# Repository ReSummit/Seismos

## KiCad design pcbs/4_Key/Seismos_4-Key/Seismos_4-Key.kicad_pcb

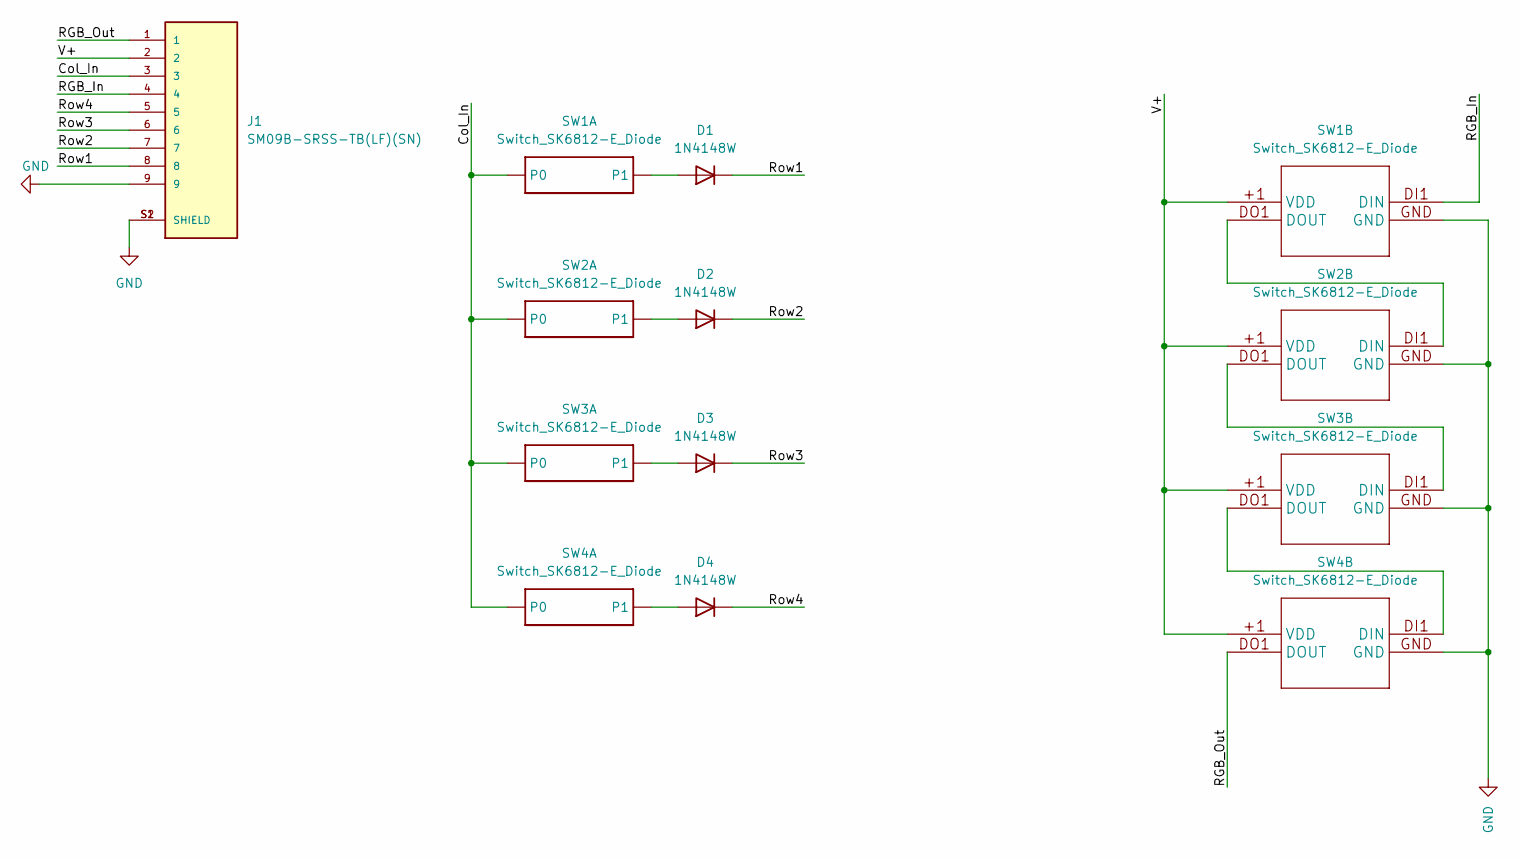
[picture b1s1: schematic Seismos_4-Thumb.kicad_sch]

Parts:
D1, D2, D3, D4: 1N4148W; D_SOD-123
J1: SM09B-SRSS-TB(LF)(SN); JST_SM09B-SRSS-TB(LF)(SN); PARTREV 1.0
SW1, SW2, SW3, SW4: Switch_SK6812-E_Diode

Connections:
/Col_In: J1.3, SW1.CHOC2 (P0), SW1.MX2 (P0), SW2.CHOC2 (P0), SW2.MX2 (P0), SW3.CHOC2 (P0), SW3.MX2 (P0), SW4.CHOC2 (P0), SW4.MX2 (P0)
/RGB_In: J1.4, SW1.DI1 (DIN)
/RGB_Out: J1.1, SW4.DO1 (DOUT)
/Row1: D1.1 (K), J1.8
/Row2: D2.1 (K), J1.7
/Row3: D3.1 (K), J1.6
/Row4: D4.1 (K), J1.5
/V+: J1.2, SW1.+1 (VDD), SW2.+1 (VDD), SW3.+1 (VDD), SW4.+1 (VDD)
GND: J1.9, J1.S1 (SHIELD), J1.S2 (SHIELD), SW1.GND, SW2.GND, SW3.GND, SW4.GND
unnamed: D1.2 (A), SW1.CHOC1 (P1), SW1.MX1 (P1)
unnamed: D2.2 (A), SW2.CHOC1 (P1), SW2.MX1 (P1)
unnamed: D3.2 (A), SW3.CHOC1 (P1), SW3.MX1 (P1)
unnamed: D4.2 (A), SW4.CHOC1 (P1), SW4.MX1 (P1)
unnamed: SW1.DO1 (DOUT), SW2.DI1 (DIN)
unnamed: SW2.DO1 (DOUT), SW3.DI1 (DIN)
unnamed: SW3.DO1 (DOUT), SW4.DI1 (DIN)

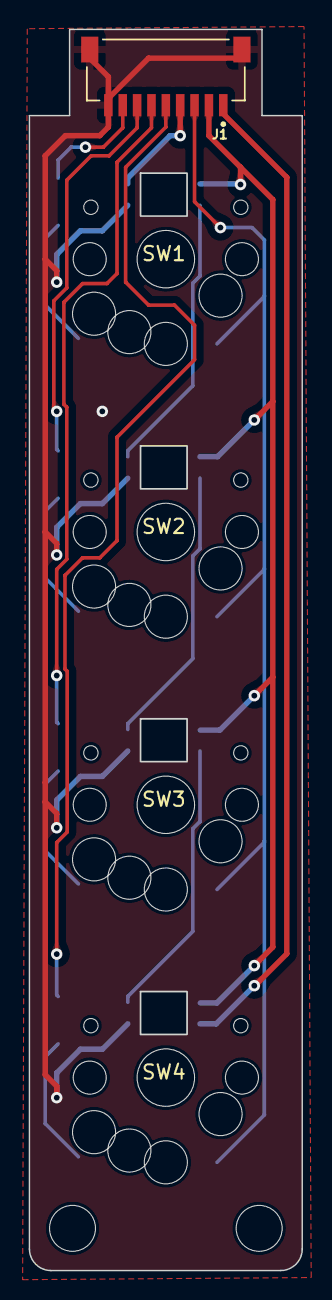
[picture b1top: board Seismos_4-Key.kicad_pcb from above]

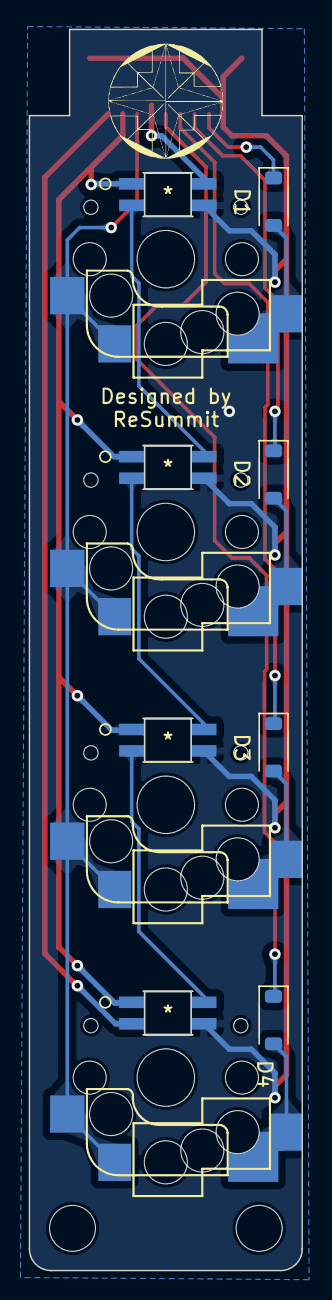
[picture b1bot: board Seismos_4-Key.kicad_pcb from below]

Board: 2 copper layers, 19.0 x 86.4 mm, 9 parts (4 on the bottom side), 16 nets.

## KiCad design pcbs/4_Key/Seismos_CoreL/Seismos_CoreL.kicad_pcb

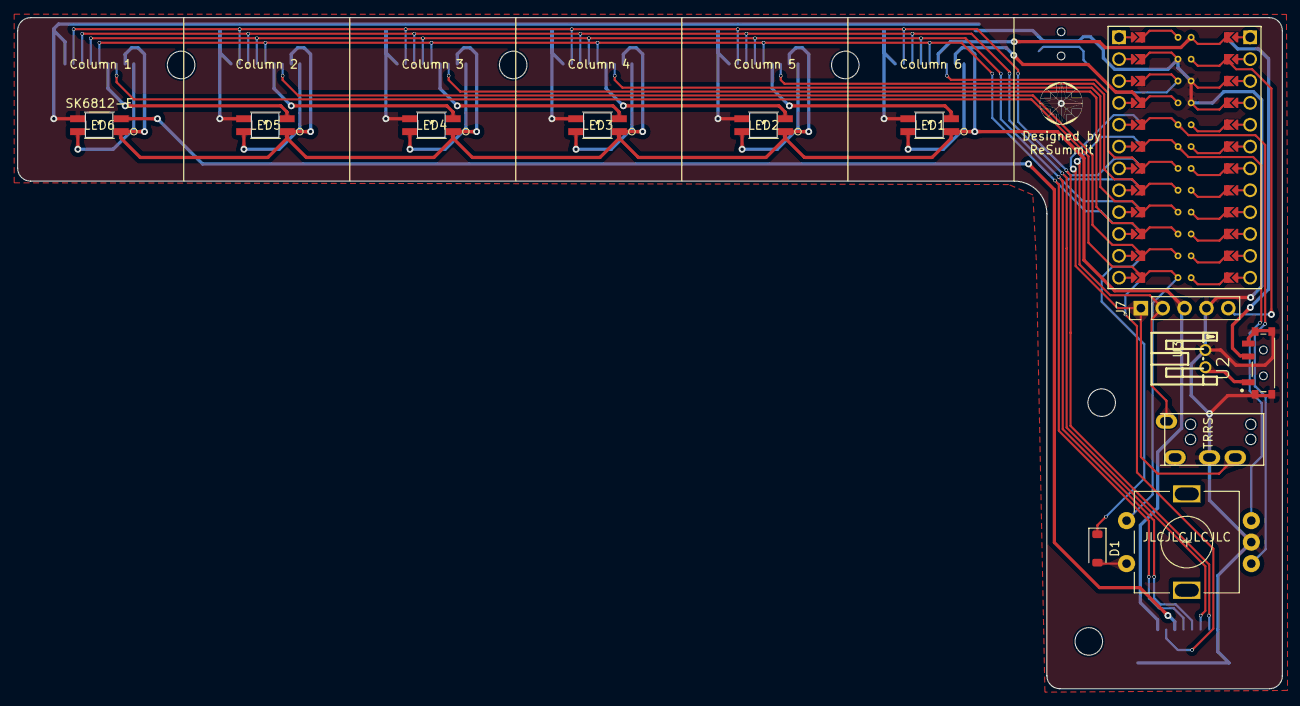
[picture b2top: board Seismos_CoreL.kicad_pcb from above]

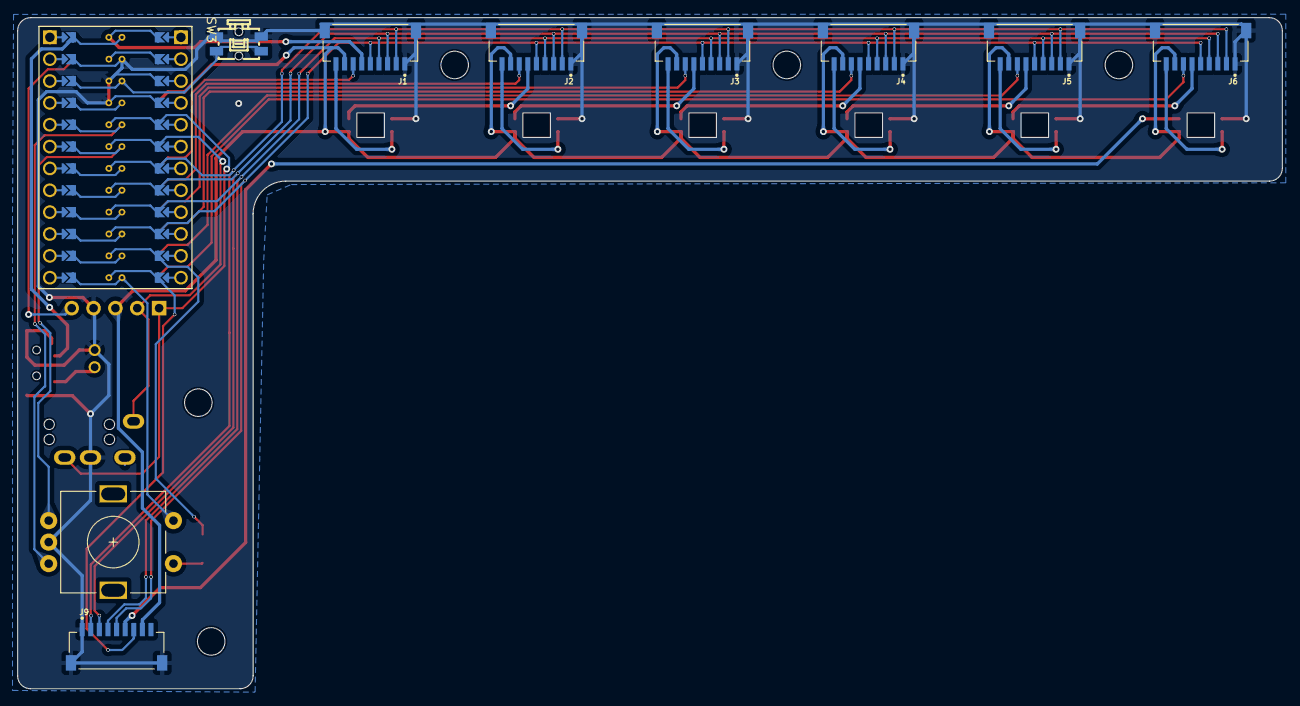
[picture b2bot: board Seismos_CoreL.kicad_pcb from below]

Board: 2 copper layers, 147.0 x 78.0 mm, 23 parts (14 on the bottom side), 36 nets.

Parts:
2, 4: Hole_M3_3.2mm
D1: 1N4148W; D_SOD-123
J1, J2, J3, J4, J5, J6, J9: SM09B-SRSS-TB(LF)(SN); JST_SM09B-SRSS-TB(LF)(SN)
J7: Conn_01x05_Pin; PinHeader_1x05_P2.54mm_Vertical
J8: MJ-4PP-9-Lily58; MJ-4PP-9
LED1, LED2, LED3, LED4, LED5, LED6: SK6812-E
SW1: RotaryEncoder_Switch; RotaryEncoder_Alps_EC11E-Switch_Vertical_H20mm-keebio_modif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
SW3: EVQPUC02K; SW-SMD_EVQPUD02K
U1: ProMicro_2-Lily58-cache-Lily58_Pro-rescue; ProMicro
U2: MSK-12C02_SMD_SPDT_SWITCH; SW_PCM12SMTR
U3: S2B-PH-K-S-GW; CONN-TH_S2B-PH-K-S-GW

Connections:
/Col_In1: J1.7, U1.18 (A1(PF6))
/Col_In2: J2.7, U1.17 (A0(PF7))
/Col_In3: J3.7, U1.16 (D15(PB1))
/Col_In4: J4.7, U1.15 (D14(PB3))
/Col_In5: J5.7, U1.14 (D16(PB2))
/Col_In6: J6.7, SW1.S1, U1.13 (D10(PB6))
/Col_InT: J9.7, U1.12 (D9(PB5))
/RGB_In1: J1.6, U1.1 (TX(PD3))
/RGB_In2: J2.6, LED1.2 (DOUT)
/RGB_In3: J3.6, LED2.2 (DOUT)
/RGB_In4: J4.6, LED3.2 (DOUT)
/RGB_In5: J5.6, LED4.2 (DOUT)
/RGB_In6: J6.6, LED5.2 (DOUT)
/RGB_In7: J9.6, LED6.2 (DOUT)
/RGB_Out1: J1.9, LED1.4 (DIN)
/RGB_Out2: J2.9, LED2.4 (DIN)
/RGB_Out3: J3.9, LED3.4 (DIN)
/RGB_Out4: J4.9, LED4.4 (DIN)
/RGB_Out5: J5.9, LED5.4 (DIN)
/RGB_Out6: J6.9, LED6.4 (DIN)
/Row1: J1.2, J2.2, J3.2, J4.2, J5.2, J6.2, J9.2, U1.7 (D4(PD4))
/Row2: J1.3, J2.3, J3.3, J4.3, J5.3, J6.3, J9.3, U1.8 (D5(PC6))
/Row3: J1.4, J2.4, J3.4, J4.4, J5.4, J6.4, J9.4, U1.9 (D6(PD7))
/Row4: J1.5, J2.5, J3.5, J4.5, J5.5, J6.5, J9.5, U1.10 (D7(PE6))
/RowT: D1.1 (K), U1.11 (D8(PB4))
/V+: J1.8, J2.8, J3.8, J4.8, J5.8, J6.8, J7.3, J9.8, LED1.1 (VDD), LED2.1 (VDD), LED3.1 (VDD), LED4.1 (VDD), LED5.1 (VDD), LED6.1 (VDD), U1.21 (VCC)
/V_bat: U1.24 (RAW), U2.COM
CS: J7.5, U1.2 (RX(PD2))
ENCA: SW1.A, U1.20 (A3(PF4))
ENCB: SW1.B, U1.19 (A2(PF5))
GND: J1.1, J1.S1 (SHIELD), J1.S2 (SHIELD), J2.1, J2.S1 (SHIELD), J2.S2 (SHIELD), J3.1, J3.S1 (SHIELD), J3.S2 (SHIELD), J4.1, J4.S1 (SHIELD), J4.S2 (SHIELD), J5.1, J5.S1 (SHIELD), J5.S2 (SHIELD), J6.1, J6.S1 (SHIELD), J6.S2 (SHIELD), J7.4, J8.2, J9.1, J9.S1 (SHIELD), J9.S2 (SHIELD), LED1.3 (GND), LED2.3 (GND), LED3.3 (GND), LED4.3 (GND), LED5.3 (GND), LED6.3 (GND), SW1.C, SW3.2, SW3.4, U1.3 (GND), U1.4 (GND), U1.23 (GND), U2.GND, U2.L1, U3.1
unnamed: D1.2 (A), SW1.S2
unnamed: U2.L2, U3.2
RESET: SW3.1, SW3.3, U1.22 (RST)
SCL: J7.2, J8.4, U1.6 (SCL(PD0))
SDA: J7.1, J8.3, U1.5 (SDA(PD1))

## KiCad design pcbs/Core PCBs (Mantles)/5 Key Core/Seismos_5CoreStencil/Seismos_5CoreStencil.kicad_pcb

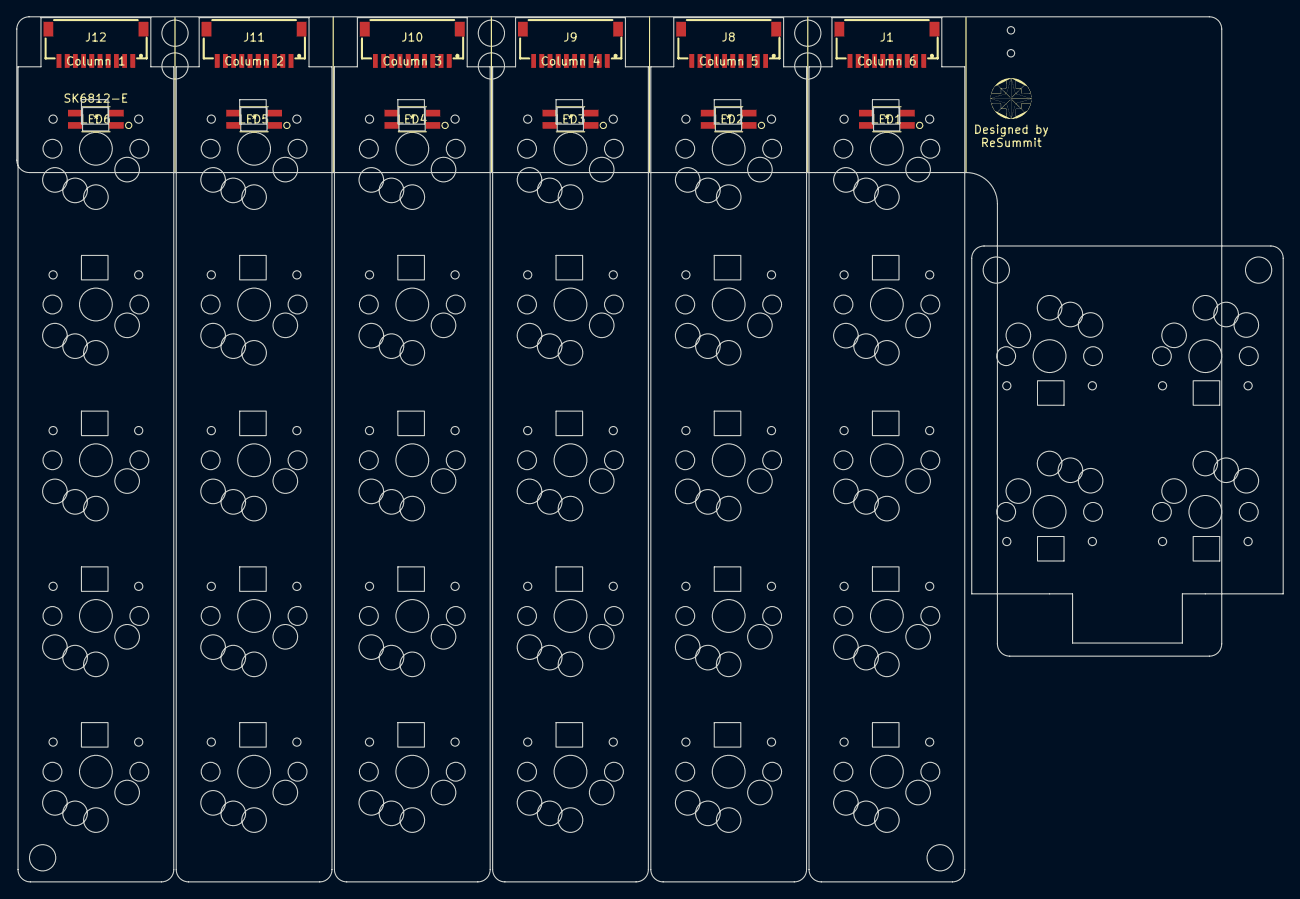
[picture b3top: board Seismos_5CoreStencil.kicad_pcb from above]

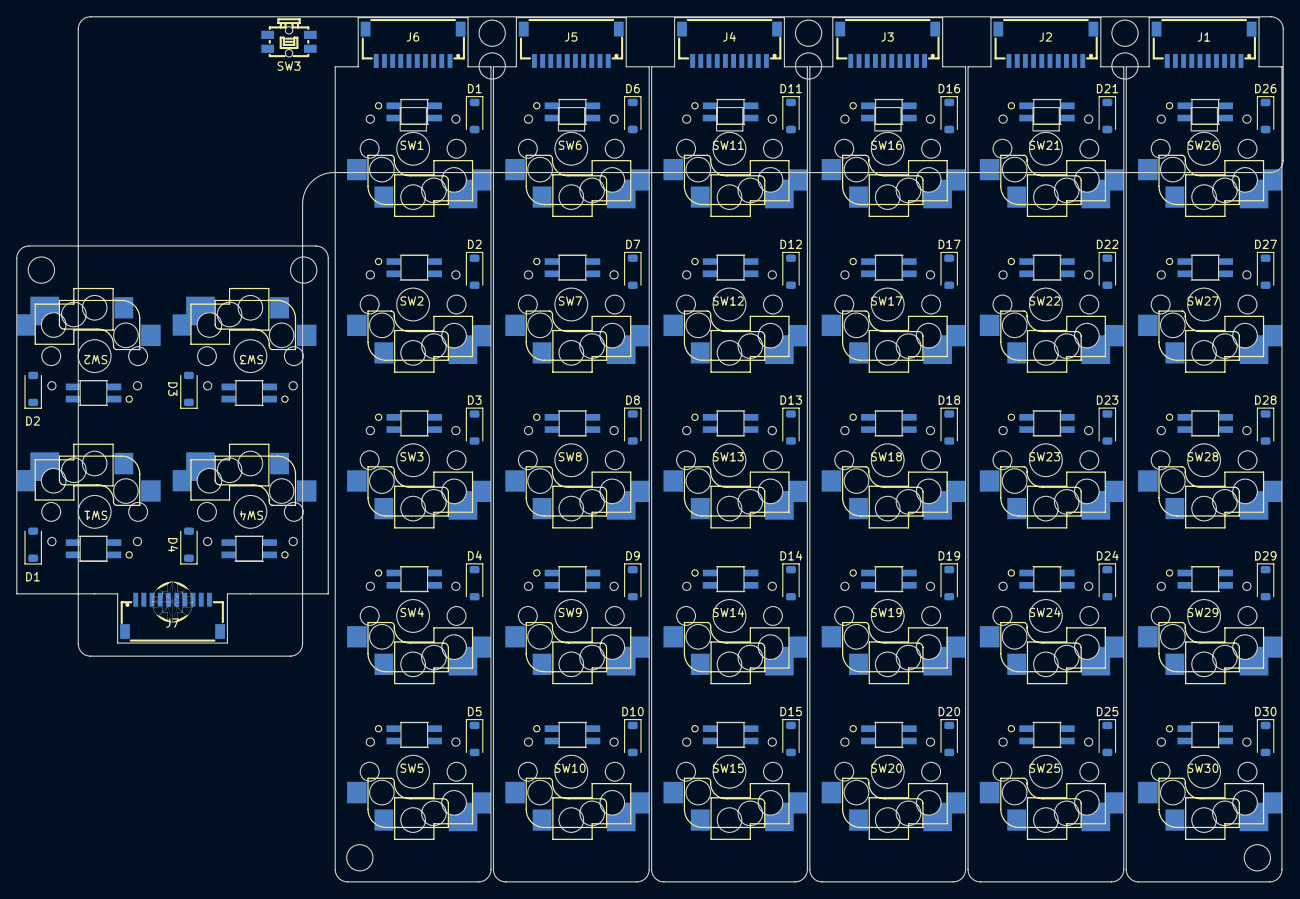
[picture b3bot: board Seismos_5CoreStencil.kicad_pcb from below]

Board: 2 copper layers, 154.5 x 105.5 mm, 91 parts (82 on the bottom side), 20 nets, no tracks yet.

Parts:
2, 4, 4#2: Hole_M3_3.2mm
D1, D1#2, D2, D2#2, D3, D3#2, D4, D4#2, D5, D6, D7, D8, D9, D10, D11, D12, D13, D14, D15, D16, D17, D18, D19, D20, D21, D22, D23, D24, D25, D26, D27, D28, D29, D30: 1N4148W; D_SOD-123
J1, J8, J9, J10, J11, J12: SM10B-SRSS-TB_(LF)(SN); CONN-SMD_10P-P1.00_SM10B-SRSS-TB-LF-SN
J1#2, J2, J3, J4, J5, J6, J7: SM09B-SRSS-TB(LF)(SN); CONN-SMD_10P-P1.00_SM10B-SRSS-TB-LF-SN
LED1, LED2, LED3, LED4, LED5, LED6: SK6812-E
SW1, SW1#2, SW2, SW2#2, SW3, SW3#3, SW4, SW4#2, SW5, SW6, SW7, SW8, SW9, SW10, SW11, SW12, SW13, SW14, SW15, SW16, SW17, SW18, SW19, SW20, SW21, SW22, SW23, SW24, SW25, SW26, SW27, SW28, SW29, SW30: Switch_SK6812-E_Diode
SW3#2: EVQPUC02K; SW-SMD_EVQPUD02K

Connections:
/RGB_In2: J5.7, LED1.2 (DOUT)
/RGB_In3: J4.7, LED2.2 (DOUT)
/RGB_In4: J3.7, LED3.2 (DOUT)
/RGB_In5: J2.7, LED4.2 (DOUT)
/RGB_In6: J1#2.7, LED5.2 (DOUT)
/RGB_In7: J7.7, LED6.2 (DOUT)
/RGB_Out1: J6.10, LED1.4 (DIN)
/RGB_Out2: J5.10, LED2.4 (DIN)
/RGB_Out3: J4.10, LED3.4 (DIN)
/RGB_Out4: J3.10, LED4.4 (DIN)
/RGB_Out5: J2.10, LED5.4 (DIN)
/RGB_Out6: J1#2.10, LED6.4 (DIN)
/Row1: D1.1 (K), D1#2.1 (K), D6.1 (K), D11.1 (K), D16.1 (K), D21.1 (K), D26.1 (K), J1.6, J1#2.5, J2.5, J3.5, J4.5, J5.5, J6.5, J7.5, J8.6, J9.6, J10.6, J11.6, J12.6
/Row2: D2.1 (K), D2#2.1 (K), D7.1 (K), D12.1 (K), D17.1 (K), D22.1 (K), D27.1 (K), J1.7, J1#2.4, J2.4, J3.4, J4.4, J5.4, J6.4, J7.4, J8.7, J9.7, J10.7, J11.7, J12.7
/Row3: D3.1 (K), D3#2.1 (K), D8.1 (K), D13.1 (K), D18.1 (K), D23.1 (K), D28.1 (K), J1.8, J1#2.3, J2.3, J3.3, J4.3, J5.3, J6.3, J7.3, J8.8, J9.8, J10.8, J11.8, J12.8
/Row4: D4.1 (K), D4#2.1 (K), D9.1 (K), D14.1 (K), D19.1 (K), D24.1 (K), D29.1 (K), J1.9, J1#2.2, J2.2, J3.2, J4.2, J5.2, J6.2, J7.2, J8.9, J9.9, J10.9, J11.9, J12.9
/Row5: D5.1 (K), D10.1 (K), D15.1 (K), D20.1 (K), D25.1 (K), D30.1 (K), J1.10, J1#2.1, J2.1, J3.1, J4.1, J5.1, J6.1, J8.10, J9.10, J10.10, J11.10, J12.10
/V+: J1.2, J1#2.9, J2.9, J3.9, J4.9, J5.9, J6.9, J7.9, J8.2, J9.2, J10.2, J11.2, J12.2, LED1.1 (VDD), LED2.1 (VDD), LED3.1 (VDD), LED4.1 (VDD), LED5.1 (VDD), LED6.1 (VDD), SW1.+1 (VDD), SW1#2.+1 (VDD), SW2.+1 (VDD), SW2#2.+1 (VDD), SW3.+1 (VDD), SW3#3.+1 (VDD), SW4.+1 (VDD), SW4#2.+1 (VDD), SW5.+1 (VDD), SW6.+1 (VDD), SW7.+1 (VDD), SW8.+1 (VDD), SW9.+1 (VDD), SW10.+1 (VDD), SW11.+1 (VDD), SW12.+1 (VDD), SW13.+1 (VDD), SW14.+1 (VDD), SW15.+1 (VDD), SW16.+1 (VDD), SW17.+1 (VDD), SW18.+1 (VDD), SW19.+1 (VDD), SW20.+1 (VDD), SW21.+1 (VDD), SW22.+1 (VDD), SW23.+1 (VDD), SW24.+1 (VDD), SW25.+1 (VDD), SW26.+1 (VDD), SW27.+1 (VDD), SW28.+1 (VDD), SW29.+1 (VDD), SW30.+1 (VDD)
GND: J1.5, J1.S1, J1.S2, J1#2.6, J1#2.S1, J1#2.S2, J2.6, J2.S1, J2.S2, J3.6, J3.S1, J3.S2, J4.6, J4.S1, J4.S2, J5.6, J5.S1, J5.S2, J6.6, J6.S1, J6.S2, J7.6, J7.S1, J7.S2, J8.5, J8.S1, J8.S2, J9.5, J9.S1, J9.S2, J10.5, J10.S1, J10.S2, J11.5, J11.S1, J11.S2, J12.5, J12.S1, J12.S2, LED1.3 (GND), LED2.3 (GND), LED3.3 (GND), LED4.3 (GND), LED5.3 (GND), LED6.3 (GND), SW1.GND, SW1#2.GND, SW2.GND, SW2#2.GND, SW3.GND, SW3#2.2, SW3#2.4, SW3#3.GND, SW4.GND, SW4#2.GND, SW6.GND, SW7.GND, SW8.GND, SW9.GND, SW11.GND, SW12.GND, SW13.GND, SW14.GND, SW16.GND, SW17.GND, SW18.GND, SW19.GND, SW21.GND, SW22.GND, SW23.GND, SW24.GND, SW26.GND, SW27.GND, SW28.GND, SW29.GND
RESET: SW3#2.1, SW3#2.3

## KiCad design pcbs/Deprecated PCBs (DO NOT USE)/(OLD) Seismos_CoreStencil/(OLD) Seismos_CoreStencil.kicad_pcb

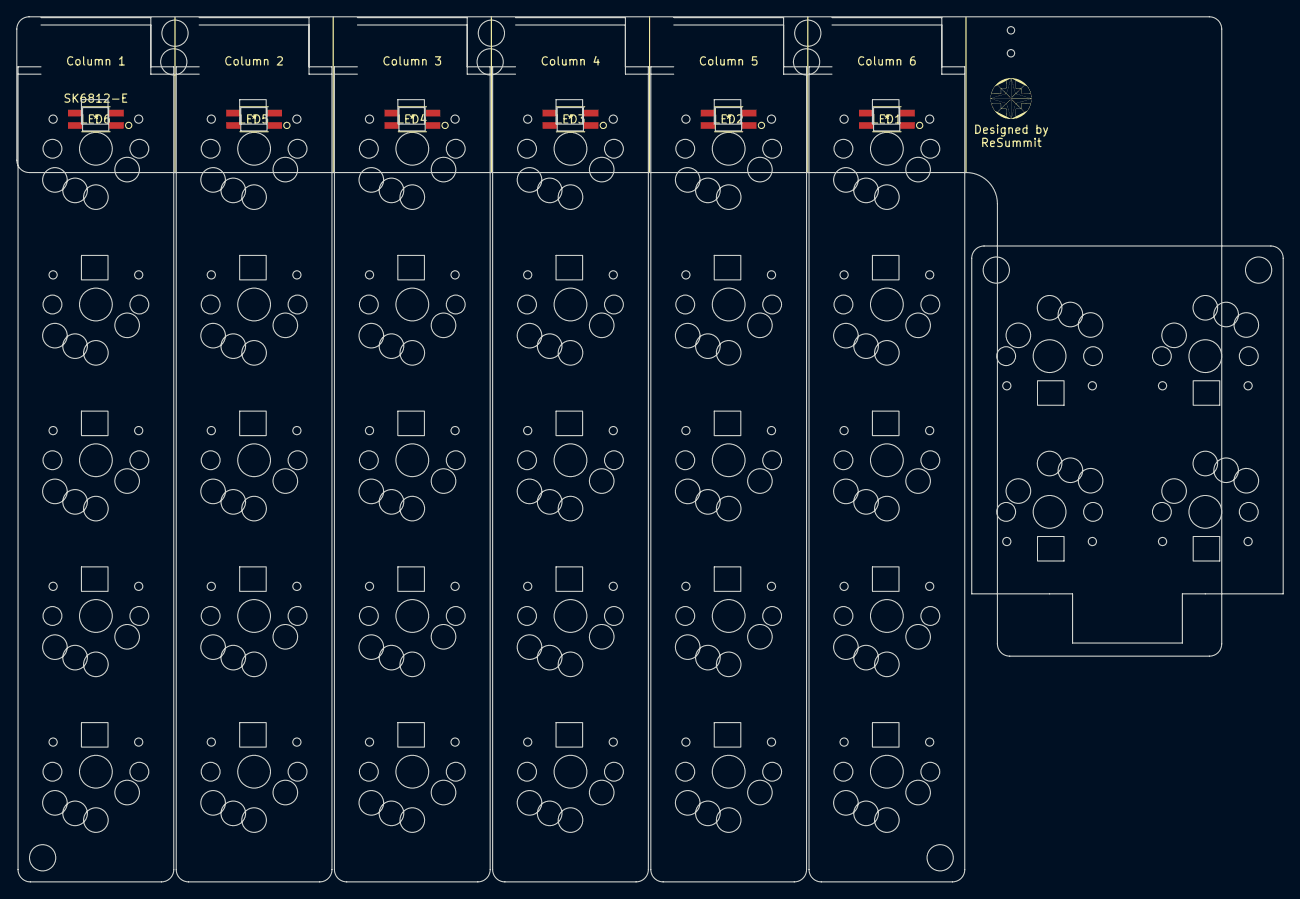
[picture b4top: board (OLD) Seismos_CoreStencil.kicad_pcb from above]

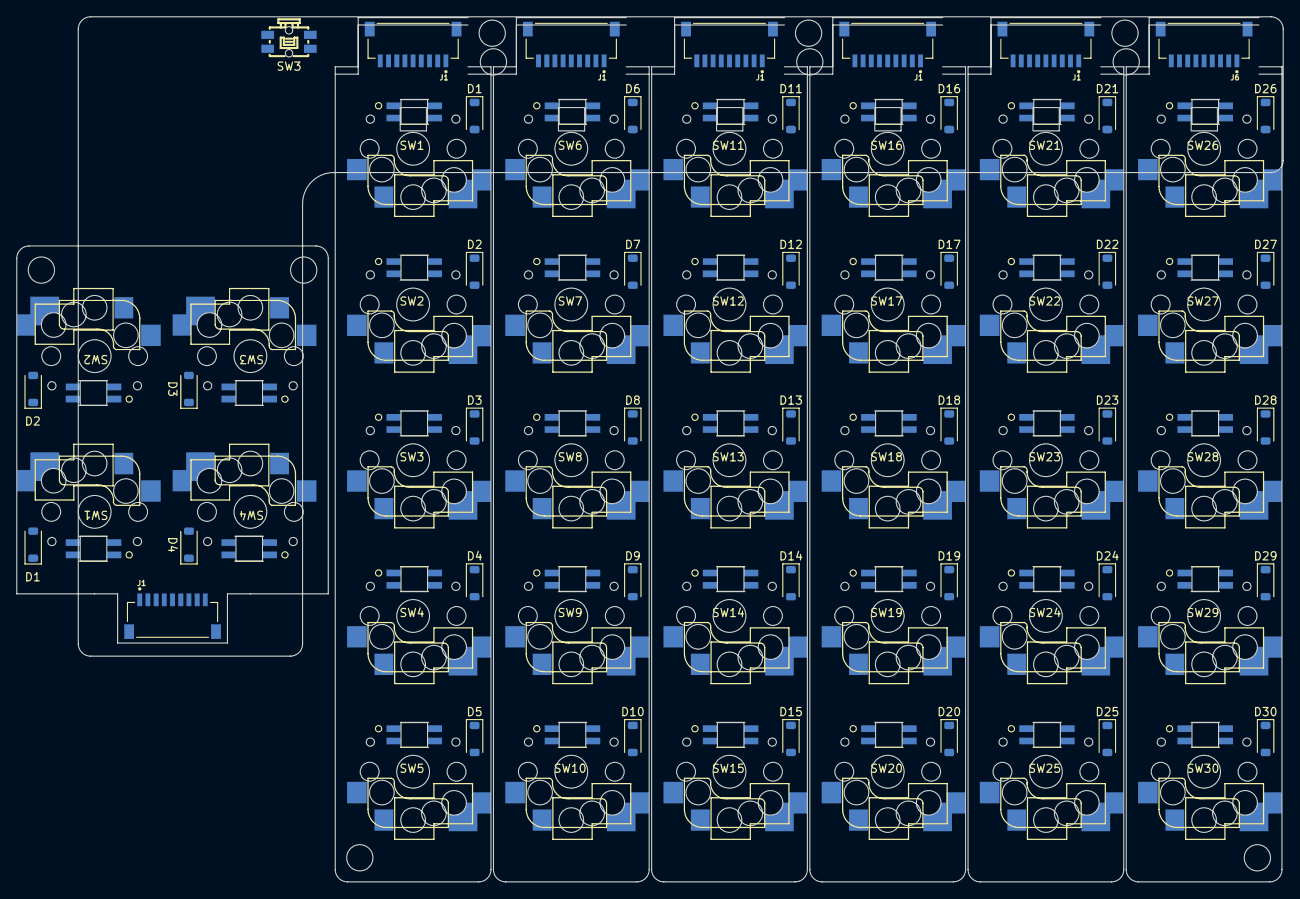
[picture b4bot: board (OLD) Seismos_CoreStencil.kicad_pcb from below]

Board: 2 copper layers, 154.5 x 105.5 mm, 83 parts (82 on the bottom side), 10 nets, no tracks yet.

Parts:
4: Hole_M3_3.2mm
D1, D1#2, D2, D2#2, D3, D3#2, D4, D4#2, D5, D6, D7, D8, D9, D10, D11, D12, D13, D14, D15, D16, D17, D18, D19, D20, D21, D22, D23, D24, D25, D26, D27, D28, D29, D30: 1N4148W; D_SOD-123
J1, J1#2, J1#3, J1#4, J1#5, J1#6, J6: SM09B-SRSS-TB(LF)(SN); JST_SM09B-SRSS-TB(LF)(SN)
LED1, LED2, LED3, LED4, LED5, LED6: SK6812-E
SW1, SW1#2, SW2, SW2#2, SW3, SW3#3, SW4, SW4#2, SW5, SW6, SW7, SW8, SW9, SW10, SW11, SW12, SW13, SW14, SW15, SW16, SW17, SW18, SW19, SW20, SW21, SW22, SW23, SW24, SW25, SW26, SW27, SW28, SW29, SW30: Switch_SK6812-E_Diode
SW3#2: EVQPUC02K; SW-SMD_EVQPUD02K

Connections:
/RGB_In6: J6.6, LED5.2 (DOUT)
/RGB_Out6: J6.9, LED6.4 (DIN)
/Row1: D1.1 (K), D1#2.1 (K), D6.1 (K), D11.1 (K), D16.1 (K), D21.1 (K), D26.1 (K), J6.2
/Row2: D2.1 (K), D2#2.1 (K), D7.1 (K), D12.1 (K), D17.1 (K), D22.1 (K), D27.1 (K), J6.3
/Row3: D3.1 (K), D3#2.1 (K), D8.1 (K), D13.1 (K), D18.1 (K), D23.1 (K), D28.1 (K), J6.4
/Row4: D4.1 (K), D4#2.1 (K), D9.1 (K), D14.1 (K), D19.1 (K), D24.1 (K), D29.1 (K), J6.5
/Row5: D5.1 (K), D10.1 (K), D15.1 (K), D20.1 (K), D25.1 (K), D30.1 (K)
/V+: J6.8, LED1.1 (VDD), LED2.1 (VDD), LED3.1 (VDD), LED4.1 (VDD), LED5.1 (VDD), LED6.1 (VDD), SW1.+1 (VDD), SW1#2.+1 (VDD), SW2.+1 (VDD), SW2#2.+1 (VDD), SW3.+1 (VDD), SW3#3.+1 (VDD), SW4.+1 (VDD), SW4#2.+1 (VDD), SW5.+1 (VDD), SW6.+1 (VDD), SW7.+1 (VDD), SW8.+1 (VDD), SW9.+1 (VDD), SW10.+1 (VDD), SW11.+1 (VDD), SW12.+1 (VDD), SW13.+1 (VDD), SW14.+1 (VDD), SW15.+1 (VDD), SW16.+1 (VDD), SW17.+1 (VDD), SW18.+1 (VDD), SW19.+1 (VDD), SW20.+1 (VDD), SW21.+1 (VDD), SW22.+1 (VDD), SW23.+1 (VDD), SW24.+1 (VDD), SW25.+1 (VDD), SW26.+1 (VDD), SW27.+1 (VDD), SW28.+1 (VDD), SW29.+1 (VDD), SW30.+1 (VDD)
GND: J6.1, J6.S1 (SHIELD), J6.S2 (SHIELD), LED1.3 (GND), LED2.3 (GND), LED3.3 (GND), LED4.3 (GND), LED5.3 (GND), LED6.3 (GND), SW1.GND, SW1#2.GND, SW2.GND, SW2#2.GND, SW3.GND, SW3#2.2, SW3#2.4, SW3#3.GND, SW4.GND, SW4#2.GND, SW6.GND, SW7.GND, SW8.GND, SW9.GND, SW11.GND, SW12.GND, SW13.GND, SW14.GND, SW16.GND, SW17.GND, SW18.GND, SW19.GND, SW21.GND, SW22.GND, SW23.GND, SW24.GND, SW26.GND, SW27.GND, SW28.GND, SW29.GND
RESET: SW3#2.1, SW3#2.3

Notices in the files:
parts and their libraries:
Copyright 2021 Accelerated Designs. All rights reserved.
